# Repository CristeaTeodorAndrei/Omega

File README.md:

# OMEGA - Flight Computer

## OMEGA is the rocket's main flight computer.

### OMEGA flight computer is equipped with an Atmega328PB microcontroller. Attached to this microcontroller is an MPU6050 gyro sensor, a LoRa module for ground telemetry. 

#### NOTE: This is the first iteration of the flight computer

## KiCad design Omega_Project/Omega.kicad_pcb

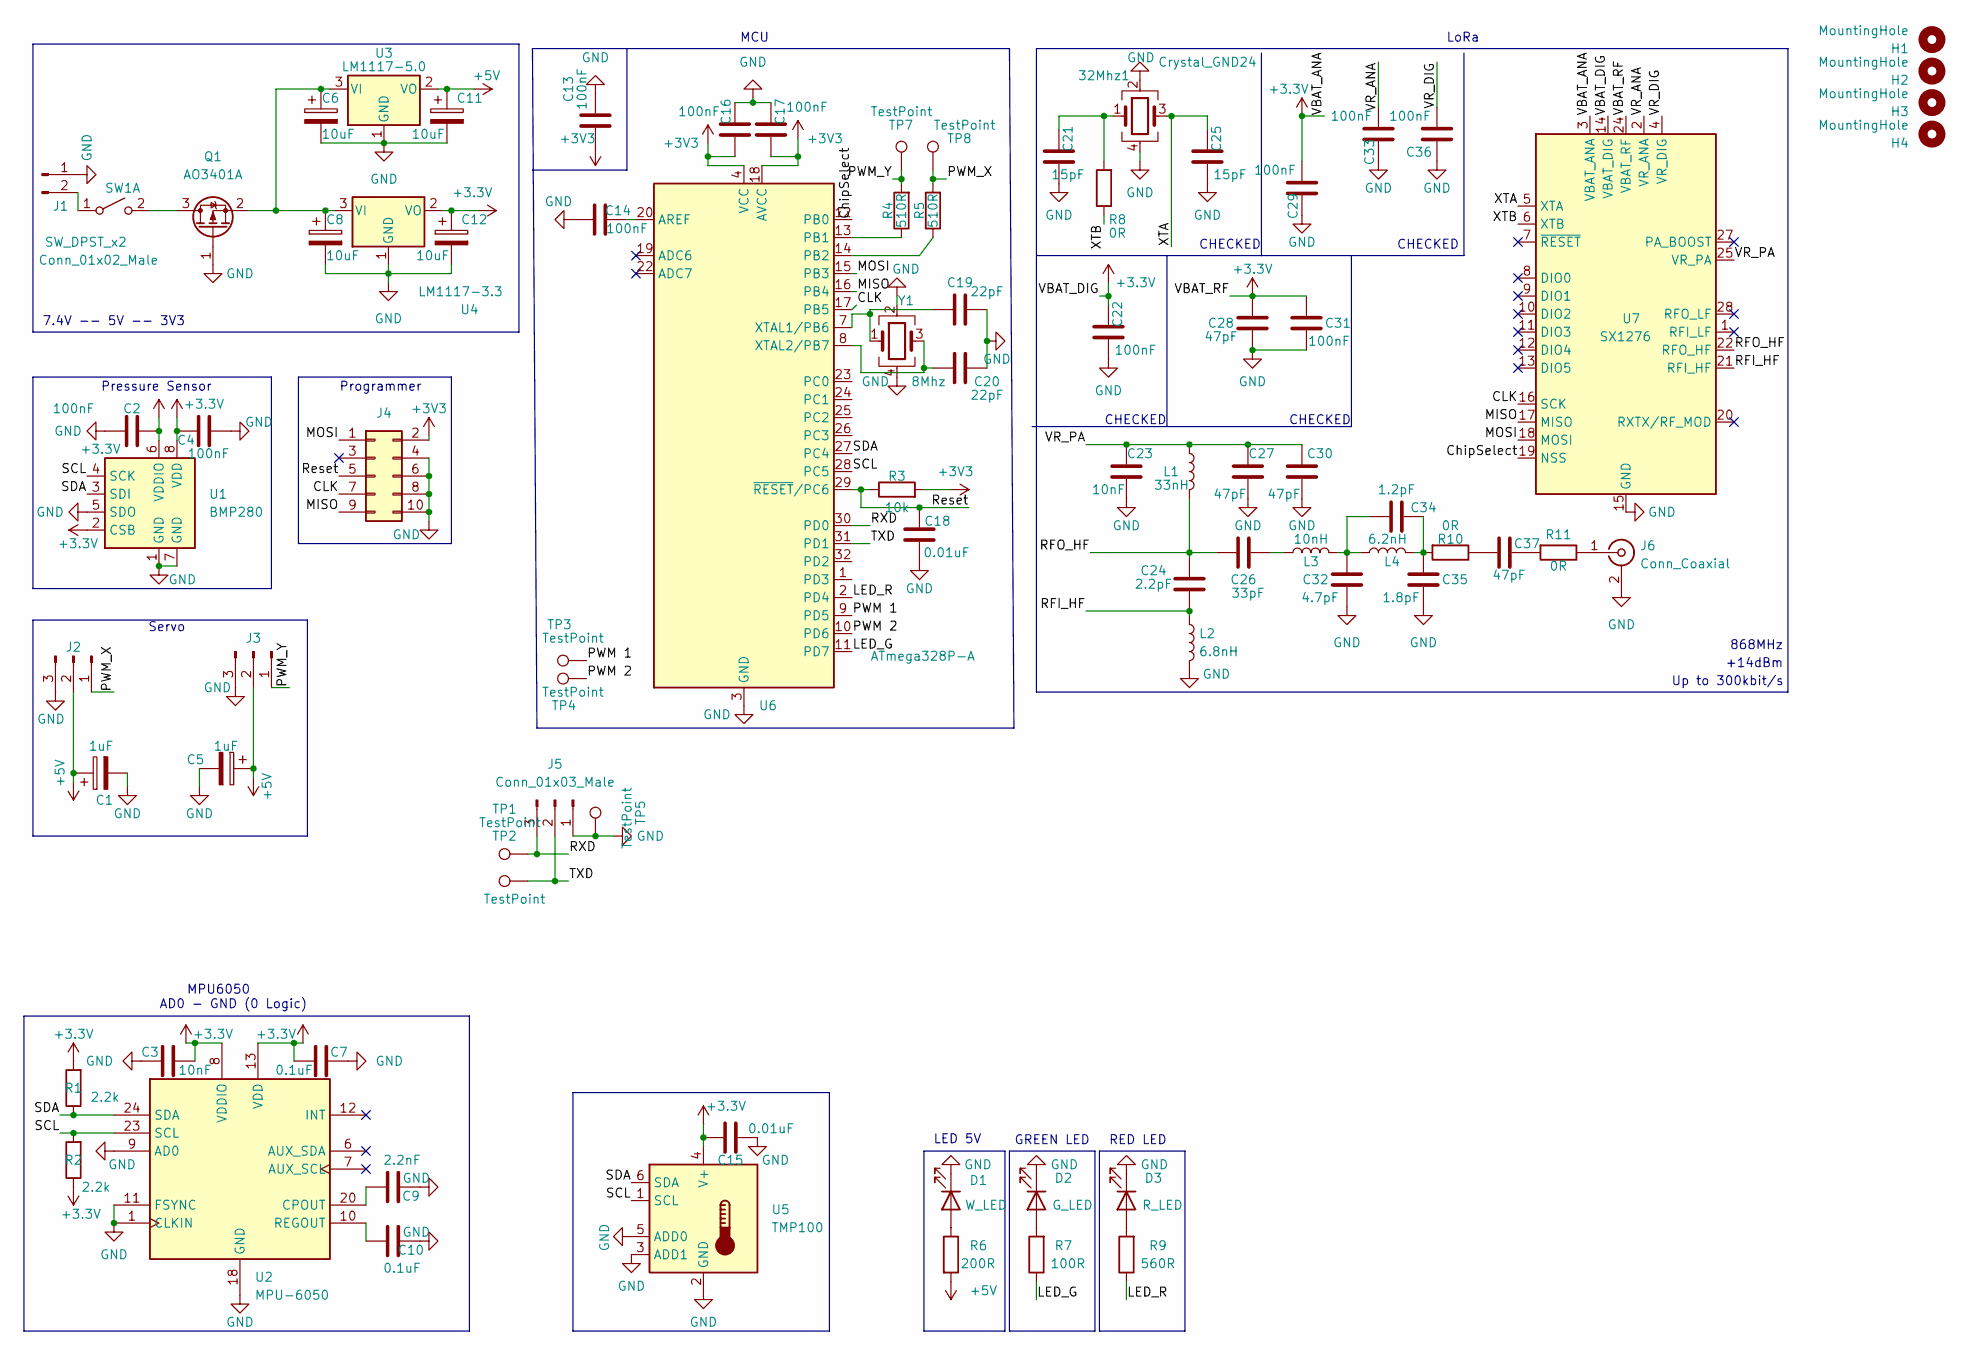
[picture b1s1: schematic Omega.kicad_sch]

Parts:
32Mhz1: Crystal_GND24; Crystal_SMD_2016-4Pin_2.0x1.6mm
C1, C5: 1uF; CP_Elec_4x5.4
C2, C4, C13, C14, C16, C17, C22, C29, C31, C33, C36: 100nF; C_0402_1005Metric
C3, C23: 10nF; C_0402_1005Metric
C6, C8, C11, C12: 10uF; C_1206_3216Metric
C7, C10: 0.1uF; C_0402_1005Metric
C9: 2.2nF; C_0402_1005Metric
C15, C18: 0.01uF; C_0402_1005Metric
C19, C20: 22pF; C_0402_1005Metric
C21, C25: 15pF; C_0402_1005Metric
C24: 2.2pF; C_0402_1005Metric
C26: 33pF; C_0402_1005Metric
C27, C28, C30, C37: 47pF; C_0402_1005Metric
C32: 4.7pF; C_0402_1005Metric
C34: 1.2pF; C_0402_1005Metric
C35: 1.8pF; C_0402_1005Metric
D1: W_LED; LED_PLCC-2
D2: G_LED; LED_PLCC-2
D3: R_LED; LED_PLCC-2
H1, H2, H3, H4: MountingHole; MountingHole_3.5mm
J1: Conn_01x02_Male; PinHeader_1x02_P2.54mm_Vertical
J2: X; PinHeader_1x03_P2.54mm_Vertical
J3: Y; PinHeader_1x03_P2.54mm_Vertical
J4: Conn_02x05_Odd_Even; IDC-Header_2x05_P2.54mm_Vertical
J5: Conn_01x03_Male; PinHeader_1x03_P2.54mm_Vertical
J6: Conn_Coaxial; SMA_Amphenol_132203-12_Horizontal
L1: 33nH; L_0402_1005Metric
L2: 6.8nH; L_0402_1005Metric
L3: 10nH; L_0402_1005Metric
L4: 6.2nH; L_0402_1005Metric
Q1: AO3401A; SOT-23
R1, R2: 2.2k; R_0402_1005Metric
R3: 10k; R_0402_1005Metric
R4, R5: 510R; R_0402_1005Metric
R6: 200R; R_0402_1005Metric
R7: 100R; R_0402_1005Metric
R8, R10, R11: 0R; R_0402_1005Metric
R9: 560R; R_0402_1005Metric
SW1: SW_DPST_x2; SW_DIP_SPSTx01_Slide_6.7x4.1mm_W6.73mm_P2.54mm_LowProfile_J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
TP1, TP2, TP3, TP4, TP5, TP7, TP8: TestPoint; TestPoint_Pad_D1.5mm
U1: BMP280; Bosch_LGA-8_2x2.5mm_P0.65mm_ClockwisePinNumbering
U2: MPU-6050; InvenSense_QFN-24_4x4mm_P0.5mm
U3: LM1117-5.0; SOT-223-3_TabPin2
U4: LM1117-3.3; SOT-223-3_TabPin2
U5: TMP100; SOT-23-6
U6: ATmega328P-A; TQFP-32_7x7mm_P0.8mm
U7: SX1276; QFN-28-1EP_6x6mm_P0.65mm_EP4.8x4.8mm
Y1: 8Mhz; Crystal_SMD_5032-4Pin_5.0x3.2mm

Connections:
+5V: C1.1, C5.1, C11.1, J2.2, J3.2, R6.2, U3.2 (VO)
/CLK: J4.7, U6.17 (PB5), U7.16 (SCK)
/ChipSelect: U6.12 (PB0), U7.19 (NSS)
/LED_G: R7.1, U6.11 (PD7)
/LED_R: R9.1, U6.2 (PD4)
/MISO: J4.9, U6.16 (PB4), U7.17 (MISO)
/MOSI: J4.1, U6.15 (PB3), U7.18 (MOSI)
/PWM 1: TP3.1, U6.9 (PD5)
/PWM 2: TP4.1, U6.10 (PD6)
/PWM_X: J2.1, R5.2, TP8.1
/PWM_Y: J3.1, R4.2, TP7.1
/RFI_HF: C24.1, L2.1, U7.21 (RFI_HF)
/RFO_HF: C24.2, C26.2, L1.2, U7.22 (RFO_HF)
/RXD: J5.3, TP1.1, U6.30 (PD0)
/Reset: C18.1, J4.5, R3.1, U6.29 (~RESET/PC6)
/SCL: R2.2, U1.4 (SCK), U2.23 (SCL), U5.1 (SCL), U6.28 (PC5)
/SDA: R1.1, U1.3 (SDI), U2.24 (SDA), U5.6 (SDA), U6.27 (PC4)
/TXD: J5.2, TP2.1, U6.31 (PD1)
/VR_ANA: C33.1, U7.2 (VR_ANA)
/VR_DIG: C36.1, U7.4 (VR_DIG)
/VR_PA: C23.2, C27.2, C30.2, L1.1, U7.25 (VR_PA)
/XTA: 32Mhz1.3, C25.2, U7.5 (XTA)
/XTB: R8.1, U7.6 (XTB)
GND: 32Mhz1.2, 32Mhz1.4, C1.2, C2.1, C3.1, C4.1, C5.2, C6.2, C7.2, C8.2, C9.2, C10.2, C11.2, C12.2, C13.2, C14.1, C15.2, C16.2, C17.2, C18.2, C19.2, C20.2, C21.1, C22.1, C23.1, C25.1, C27.1, C28.1, C29.2, C30.1, C31.1, C32.2, C33.2, C35.2, C36.2, D1.1 (K), D2.1 (K), D3.1 (K), J1.1, J2.3, J3.3, J4.4, J4.6, J4.8, J4.10, J5.1, J6.2 (Ext), L2.2, Q1.1 (G), TP5.1, U1.1 (GND), U1.5 (SDO), U1.7 (GND), U2.1 (CLKIN), U2.9 (AD0), U2.11 (FSYNC), U2.18 (GND), U3.1 (GND), U4.1 (GND), U5.2 (GND), U5.3 (ADD1), U5.5 (ADD0), U6.3 (GND), U6.5 (GND), U6.21 (GND), U7.15 (GND), U7.23 (GND), U7.26 (GND), U7.29 (GND), Y1.2, Y1.4
unnamed: 32Mhz1.1, C21.2, R8.2
unnamed: C6.1, C8.1, Q1.2 (S), U3.3 (VI), U4.3 (VI)
unnamed: C9.1, U2.20 (CPOUT)
unnamed: C10.1, U2.10 (REGOUT)
unnamed: C14.2, U6.20 (AREF)
unnamed: C19.1, U6.7 (XTAL1/PB6), Y1.1
unnamed: C20.1, U6.8 (XTAL2/PB7), Y1.3
unnamed: C26.1, L3.1
unnamed: C32.1, C34.2, L3.2, L4.1
unnamed: C34.1, C35.1, L4.2, R10.2
unnamed: C37.1, R10.1
unnamed: C37.2, R11.2
unnamed: D1.2 (A), R6.1
unnamed: D2.2 (A), R7.2
unnamed: D3.2 (A), R9.2
unnamed: J1.2, SW1.1 (A)
unnamed: J6.1 (In), R11.1
unnamed: Q1.3 (D), SW1.2 (B)
unnamed: R4.1, U6.13 (PB1)
unnamed: R5.1, U6.14 (PB2)

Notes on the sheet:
CHECKED
LED 5V
868MHz
Pressure Sensor
Up to 300kbit/s
Programmer
MPU6050 AD0 - GND (0 Logic)
MCU
RED LED
+14dBm
7.4V -- 5V -- 3V3
Servo
GREEN LED
LoRa

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
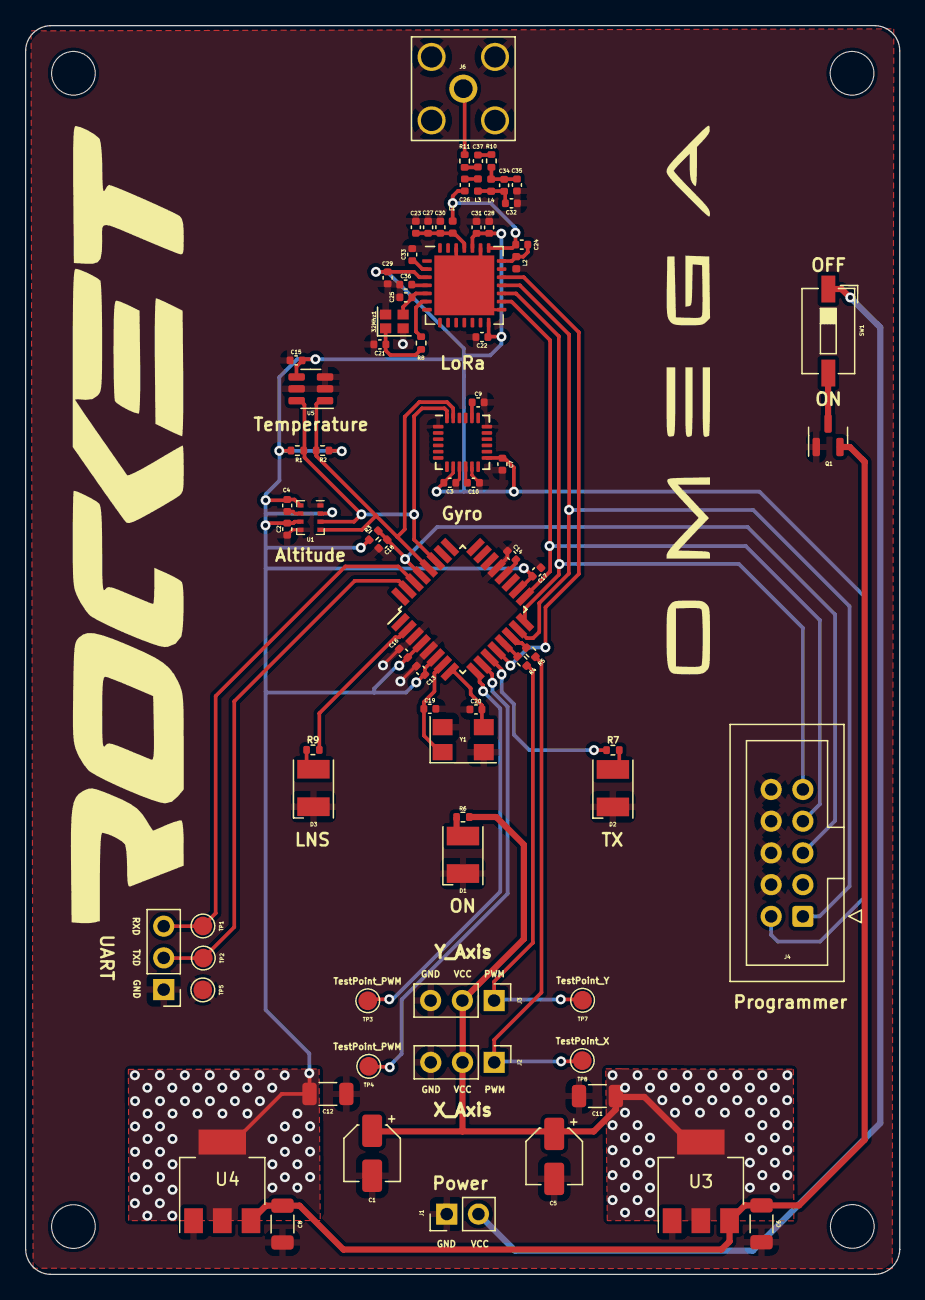
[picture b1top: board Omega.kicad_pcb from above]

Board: 2 copper layers, 70.0 x 100.0 mm, 84 parts (0 on the bottom side), 45 nets.

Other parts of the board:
G2: LOGO; Logo

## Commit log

2022-11-28 Added Omega project
2022-11-28 Modified README.md
2023-03-11 Updated Readme file

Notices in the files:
Omega_Project/Omega.kicad_pcb:
© Cristea Teodor - Andrei
